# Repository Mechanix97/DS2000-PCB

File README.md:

<h1 align="center">DS2000 PCB</h1>

<p align="center">
  <b>Three keys for Discord: mute, deafen, disconnect.</b><br>
  RP2350A · Kailh Choc V1 · RGB inside the switch · USB-C (by JLC or by hand) or a soldered cable · the board <i>is</i> the top face
</p>

KiCad design for the DS2000, a three-key Discord control deck. Mute and deafen are lit from
underneath by an RGB LED; disconnect has none. The board is also the device's visible top face: the
RP2350A, the logos and the legends are meant to be seen. It sits in a 3D-printed tray
([DS2000-Enclosure](https://github.com/Mechanix97/DS2000-Enclosure)).

| | |
|---|---|
| MCU | Raspberry Pi RP2350A |
| Keys | 3× Kailh Choc V1 (low profile) in a row, 18 mm pitch, soldered, MBK-style caps. The footprint also takes 3-pin MX switches, for prototypes |
| LEDs | 2× SK6805-EC20 (2.0 × 2.0 × 0.65 mm, WS2812-compatible), on top inside the LED window of the mute and deafen switches |
| Connector | USB-C receptacle J1 on the bottom, fitted by JLC (*standard* variant) or by hand (*economic*). Or a USB cable soldered to J3's pads on the bottom. USB 2.0 full speed |
| Board | 4 layers, 1.6 mm, 72 × 46 mm, black mask, ENIG. Every part but J1 on top, RP2350A on show; underneath J1, J3's wire pads, the debug pads and the test pads |
| Tool | **KiCad 10** |

Design decisions, block descriptions, BOM and open items: [`docs/design-rev-a.md`](docs/design-rev-a.md).

## In its enclosure

The same frame-style tray works flat on the desk or on a separate 7° wedge, held by magnets. The
board screws into it through its four corner holes.

<table>
  <tr>
    <td width="50%"></td>
    <td width="50%">
      <br>
      
    </td>
  </tr>
  <tr>
    <td>Exploded: four M2 screws, the board, the tray and the 7° wedge</td>
    <td>Flat, with the USB-C leaving straight back; and on the wedge, from the side</td>
  </tr>
</table>

## The board

| Top face, without switches | Underneath |
|---|---|
|  |  |
| The visible face: RP2350A, logos and legends | J1's USB-C, J3's wire pads, debug pads (SWD, BOOT, RST) and test pads (renders from before the 2026-10-23 review) |

### Close up

| | |
|---|---|
|  |  |
| **RP2350A on show**, with the flash, the 12 MHz crystal and the core regulator around it | **Light inside the switch**: the SK6805-EC20 sits in the Choc's LED window (switch hidden here); its 100 nF hides under the keycap |
|  |  |
| **Underneath**: only the debug pads, so JLC assembles one side | **Low profile**: Choc V1 with flat caps, keycap tops ~8.7 mm above the board |

<details>
<summary>More views</summary>

| With switches and keycaps | From the back |
|---|---|
|  |  |

</details>

### Schematic

One sheet, one box per block: USB input (USB-C or soldered cable) and ESD, 3.3 V regulator, RP2350A supplies, QSPI flash, crystal
and SWD, keys, and the LED chain with its 5 V level shifter.

## Pinout

The pinout is defined by the firmware (`DS2000-Firmware/include/pins.h`). Change it there first.

| Function | GPIO |
|---|---|
| Mute key | GP0 |
| Deafen key | GP1 |
| Disconnect key | GP2 |
| LED data (WS2812-compatible chain, via 5 V level shifter) | GP5 |

## Checks

```sh
kicad-cli sch erc --severity-all DS2000.kicad_sch
kicad-cli sch export netlist --format kicadsexpr -o /tmp/ds2000.net DS2000.kicad_sch
```

CI (KiBot) runs ERC and DRC with schematic parity on every change and fails on any new error.

## Manufacturing

Every change also builds the files to order the board from JLCPCB, with assembly (artifact
`kibot-out` of the KiBot workflow):

- `JLCPCB/`: gerbers and drill (zipped), BOM with LCSC numbers, placement (CPL) with JLC's rotation fixes
- `step/`: the populated board as STEP, origin at its centre, for the [enclosure](https://github.com/Mechanix97/DS2000-Enclosure)

Board options, parts and what to check before ordering: [`docs/design-rev-a.md`](docs/design-rev-a.md#bill-of-materials).

## Related repositories

- [DS2000](https://github.com/Mechanix97/DS2000): desktop application
- [DS2000-Firmware](https://github.com/Mechanix97/DS2000-Firmware): firmware
- [DS2000-Enclosure](https://github.com/Mechanix97/DS2000-Enclosure): enclosure (Fusion 360)

## License

Copyright Mechardo Labs 2025-2026.

| What | License |
|---|---|
| The hardware design: schematic, board, footprints, symbols, 3D models, KiBot configs, docs | **CERN-OHL-S-2.0**, the strongly reciprocal CERN Open Hardware Licence v2, see [`LICENSE`](LICENSE) |
| The scripts in [`tools/`](tools) | AGPL-3.0, see [`tools/LICENSE`](tools/LICENSE) |
| The fonts in [`fonts/`](fonts) | SIL Open Font License 1.1, see the `OFL-*.txt` files there |

This source describes Open Hardware and is licensed under the CERN-OHL-S v2. You may redistribute
and modify this source and make products using it under the terms of the CERN-OHL-S v2
(https://ohwr.org/cern_ohl_s_v2.txt). This source is distributed WITHOUT ANY EXPRESS OR IMPLIED
WARRANTY, INCLUDING OF MERCHANTABILITY, SATISFACTORY QUALITY AND FITNESS FOR A PARTICULAR PURPOSE.
Please see the CERN-OHL-S v2 for applicable conditions.

Source location: https://github.com/Mechanix97/DS2000-PCB. As per CERN-OHL-S v2 section 4, should
you produce hardware based on this source, you must where practicable maintain the Source Location
visible on the external case of the product or in its documentation.

The hardware moved from AGPL-3.0 to CERN-OHL-S-2.0 in #16: the GPL family talks about source and
object code, which do not map cleanly onto schematics, gerbers and boards. The app and the firmware
stay AGPL-3.0.

The DS2000 name and the DS2000 and Mechardo Labs logos are not covered by these licenses: their use
is governed by the [trademark policy](TRADEMARKS.md). Forks are welcome under a name of their own.

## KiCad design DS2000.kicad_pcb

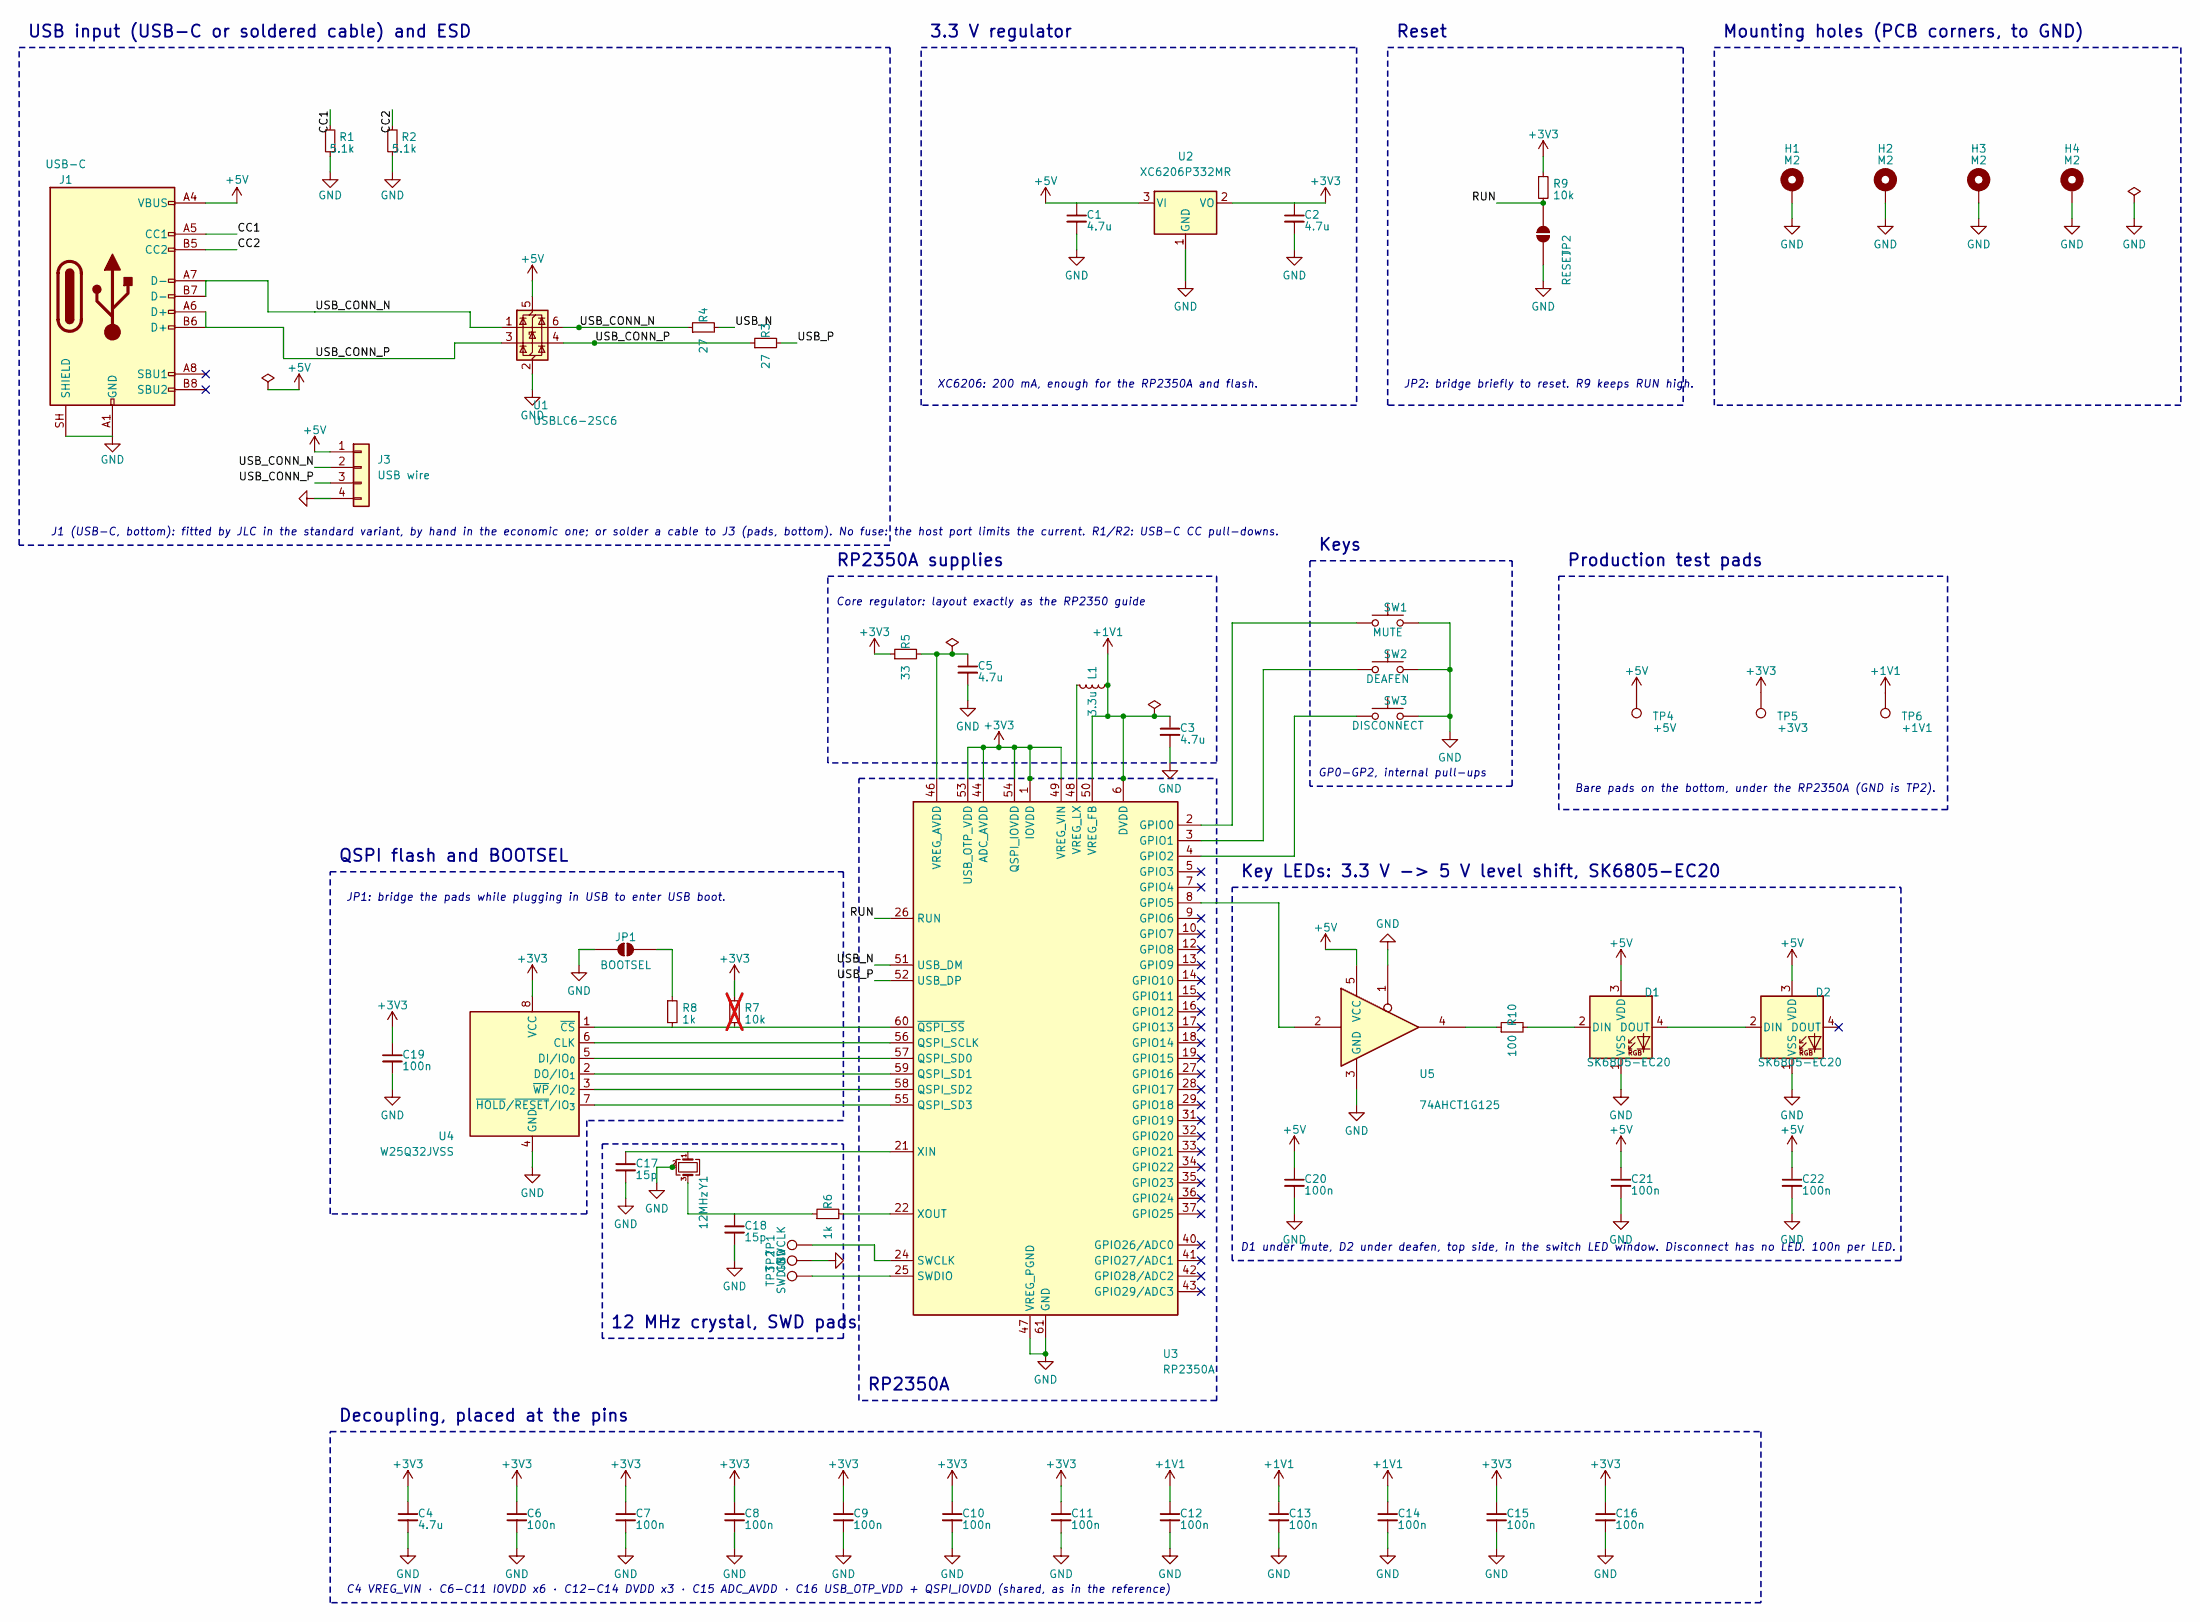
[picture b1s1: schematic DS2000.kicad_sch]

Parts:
C1, C2: 4.7u; C_0805_2012Metric; MPN CL21A475KAQNNNE; LCSC C1779
C3, C4: 4.7u; C_0402_1005Metric_Wide; MPN CL05A475MP5NRNC; LCSC C23733
C5: 4.7u; C_0402_1005Metric; MPN CL05A475MP5NRNC; LCSC C23733
C6, C7, C8, C9, C10, C11, C12, C13, C14, C15, C16, C19, C20, C21, C22: 100n; C_0402_1005Metric; MPN CL05B104KO5NNNC; LCSC C1525
C17, C18: 15p; C_0402_1005Metric; MPN 0402CG150J500NT; LCSC C1548
D1, D2: SK6805-EC20; LED_SK6805-EC20_2.0x2.0mm; MPN SK6805-EC20; LCSC C2890036
H1, H2, H3, H4: M2; MountingHole_2.2mm_M2_Pad_Via
J1: USB-C; USB_C_Receptacle_HRO_TYPE-C-31-M-12; MPN TYPE-C-31-M-12; LCSC C165948
J3: USB wire; WirePads_1x04_P2.54mm_SMD
JP1: BOOTSEL; SolderJumper-2_P1.3mm_Open_RoundedPad1.0x1.5mm
JP2: RESET; SolderJumper-2_P1.3mm_Open_RoundedPad1.0x1.5mm
L1: 3.3u; L_Abracon_AOTA-B201610S3R3-101-T; MPN AOTA-B201610S3R3-101-T; LCSC C42411119
R1, R2: 5.1k; R_0402_1005Metric; MPN 0402WGF5101TCE; LCSC C25905
R3, R4: 27; R_0402_1005Metric; MPN RC0402FR-0727RL; LCSC C138021
R5: 33; R_0402_1005Metric; MPN 0402WGF330JTCE; LCSC C25105
R6, R8: 1k; R_0402_1005Metric; MPN 0402WGF1001TCE; LCSC C11702
R7: 10k; R_0402_1005Metric; MPN 0402WGF1002TCE; LCSC C25744; not fitted
R9: 10k; R_0402_1005Metric; MPN 0402WGF1002TCE; LCSC C25744
R10: 100; R_0402_1005Metric; MPN 0402WGF1000TCE; LCSC C25076
SW1: MUTE; SW_Hybrid_Choc_V1_MX_1.00u
SW2: DEAFEN; SW_Hybrid_Choc_V1_MX_1.00u
SW3: DISCONNECT; SW_Hybrid_Choc_V1_MX_1.00u
TP1: SWCLK; TestPoint_Pad_D1.5mm
TP2: GND; TestPoint_Pad_D1.5mm
TP3: SWDIO; TestPoint_Pad_D1.5mm
TP4: +5V; TestPoint_Pad_D1.5mm
TP5: +3V3; TestPoint_Pad_D1.5mm
TP6: +1V1; TestPoint_Pad_D1.5mm
U1: USBLC6-2SC6; SOT-23-6; MPN USBLC6-2SC6; LCSC C2687116
U2: XC6206P332MR; SOT-23-3; MPN XC6206P332MR-G; LCSC C5446
U3: RP2350A; QFN-60-1EP_7x7mm_P0.4mm_EP3.4x3.4mm_ThermalVias_Drill0.3mm; MPN RP2350A; LCSC C42411118
U4: W25Q32JVSS; SOIC-8_5.3x5.3mm_P1.27mm; MPN W25Q32JVSSIQ; LCSC C179173
U5: 74AHCT1G125; SOT-353_SC-70-5; MPN SN74AHCT1G125DCKR; LCSC C350557
Y1: 12MHz; Crystal_SMD_3225-4Pin_3.2x2.5mm; MPN ABM8-272-T3; LCSC C20625731

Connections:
+1V1: C3.1, C12.1, C13.1, C14.1, L1.1, TP6.1, U3.6 (DVDD), U3.23 (DVDD), U3.39 (DVDD), U3.50 (VREG_FB)
+3V3: C2.1, C4.1, C6.1, C7.1, C8.1, C9.1, C10.1, C11.1, C15.1, C16.1, C19.1, R5.1, R7.1, R9.1, TP5.1, U2.2 (VO), U3.1 (IOVDD), U3.11 (IOVDD), U3.20 (IOVDD), U3.30 (IOVDD), U3.38 (IOVDD), U3.44 (ADC_AVDD), U3.45 (IOVDD), U3.49 (VREG_VIN), U3.53 (USB_OTP_VDD), U3.54 (QSPI_IOVDD), U4.8 (VCC)
+5V: C1.1, C20.1, C21.1, C22.1, D1.3 (VDD), D2.3 (VDD), J1.A4 (VBUS), J1.A9 (VBUS), J1.B4 (VBUS), J1.B9 (VBUS), J3.1, TP4.1, U1.5 (VBUS), U2.3 (VI), U5.5 (VCC)
/CC1: J1.A5 (CC1), R1.2
/CC2: J1.B5 (CC2), R2.2
/RUN: JP2.1 (A), R9.2, U3.26 (RUN)
/USB_CONN_N: J1.A7 (D-), J1.B7 (D-), J3.2, R4.1, U1.1 (I/O1), U1.6 (I/O1)
/USB_CONN_P: J1.A6 (D+), J1.B6 (D+), J3.3, R3.1, U1.3 (I/O2), U1.4 (I/O2)
/USB_N: R4.2, U3.51 (USB_DM)
/USB_P: R3.2, U3.52 (USB_DP)
GND: C1.2, C2.2, C3.2, C4.2, C5.2, C6.2, C7.2, C8.2, C9.2, C10.2, C11.2, C12.2, C13.2, C14.2, C15.2, C16.2, C17.2, C18.2, C19.2, C20.2, C21.2, C22.2, D1.1 (VSS), D2.1 (VSS), H1.1, H2.1, H3.1, H4.1, J1.A1 (GND), J1.A12 (GND), J1.B1 (GND), J1.B12 (GND), J1.SH (SHIELD), J3.4, JP1.1 (A), JP2.2 (B), R1.1, R2.1, SW1.2, SW2.2, SW3.2, TP2.1, U1.2 (GND), U2.1 (GND), U3.47 (VREG_PGND), U3.61 (GND), U4.4 (GND), U5.1, U5.3 (GND), Y1.2 (G), Y1.4 (G); also elsewhere on the board
unnamed: C18.1, R6.1, Y1.3
unnamed: D1.2 (DIN), R10.2
unnamed: D1.4 (DOUT), D2.2 (DIN)
unnamed: JP1.2 (B), R8.1
unnamed: R10.1, U5.4
unnamed: SW1.1, U3.2 (GPIO0)
unnamed: SW2.1, U3.3 (GPIO1)
unnamed: SW3.1, U3.4 (GPIO2)
unnamed: U3.8 (GPIO5), U5.2
unnamed: U3.56 (QSPI_SCLK), U4.6 (CLK)
unnamed: U3.57 (QSPI_SD0), U4.5 (DI/IO_{0})
unnamed: U3.59 (QSPI_SD1), U4.2 (DO/IO_{1})
unnamed: U3.58 (QSPI_SD2), U4.3 (~WP/IO_{2})
unnamed: U3.55 (QSPI_SD3), U4.7 (~HOLD/~RESET/IO_{3})
unnamed: TP1.1, U3.24 (SWCLK)
unnamed: TP3.1, U3.25 (SWDIO)
unnamed: C5.1, R5.2, U3.46 (VREG_AVDD)
unnamed: L1.2, U3.48 (VREG_LX)
unnamed: C17.1, U3.21 (XIN), Y1.1
unnamed: R6.2, U3.22 (XOUT)
unnamed: R7.2, R8.2, U3.60 (~QSPI_SS), U4.1 (~CS)

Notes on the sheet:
C4 VREG_VIN · C6-C11 IOVDD x6 · C12-C14 DVDD x3 · C15 ADC_AVDD · C16 USB_OTP_VDD + QSPI_IOVDD (shared, as in the reference)
3.3 V regulator
J1 (USB-C, bottom): fitted by JLC in the standard variant, by hand in the economic one; or solder a cable to J3 (pads, bottom). No fuse: the host port limits the current. R1/R2: USB-C CC pull-downs.
Keys
RP2350A
Reset
RP2350A supplies
D1 under mute, D2 under deafen, top side, in the switch LED window. Disconnect has no LED. 100n per LED.
12 MHz crystal, SWD pads
GP0-GP2, internal pull-ups
QSPI flash and BOOTSEL
Decoupling, placed at the pins
Core regulator: layout exactly as the RP2350 guide
Mounting holes (PCB corners, to GND)
JP1: bridge the pads while plugging in USB to enter USB boot.
JP2: bridge briefly to reset. R9 keeps RUN high.
Key LEDs: 3.3 V -> 5 V level shift, SK6805-EC20
XC6206: 200 mA, enough for the RP2350A and flash.
USB input (USB-C or soldered cable) and ESD
Production test pads
Bare pads on the bottom, under the RP2350A (GND is TP2).

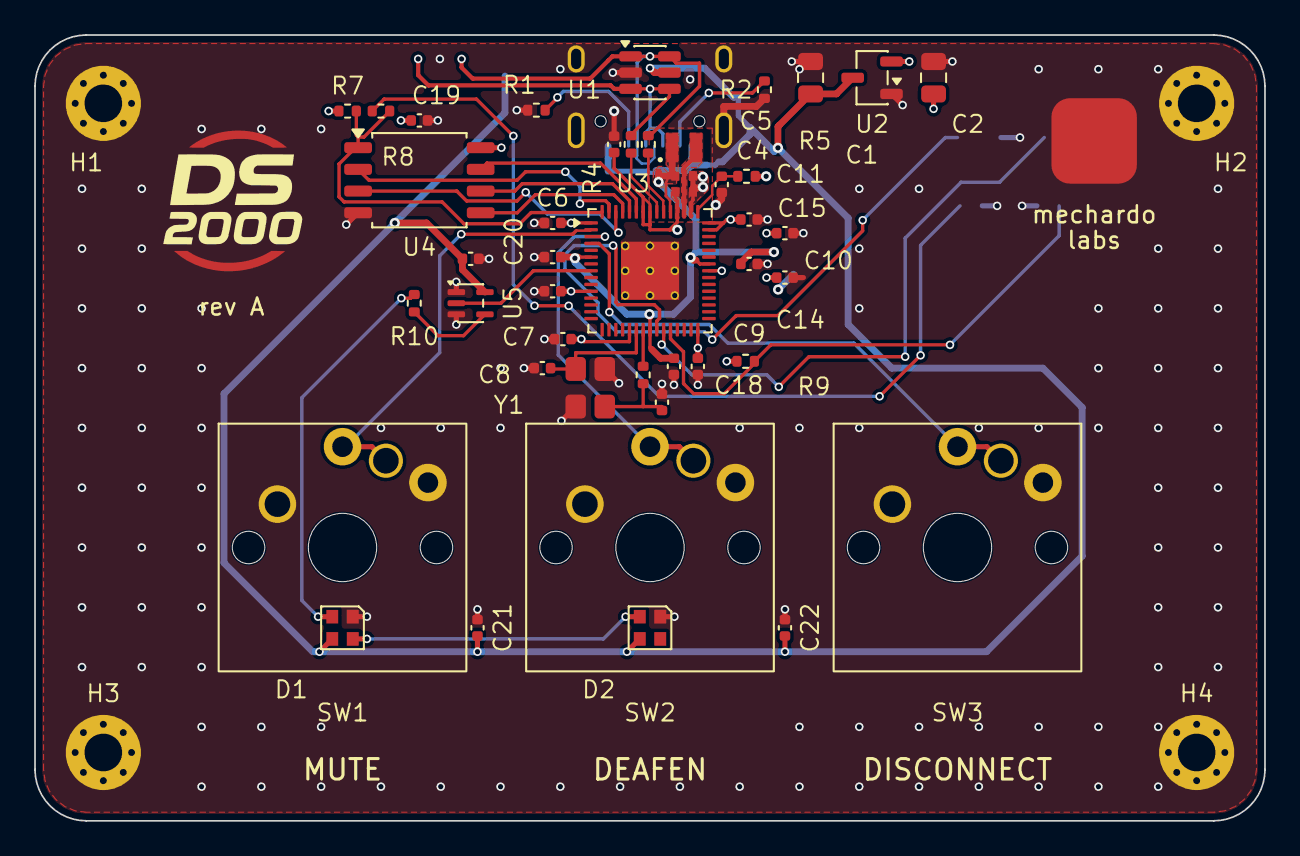
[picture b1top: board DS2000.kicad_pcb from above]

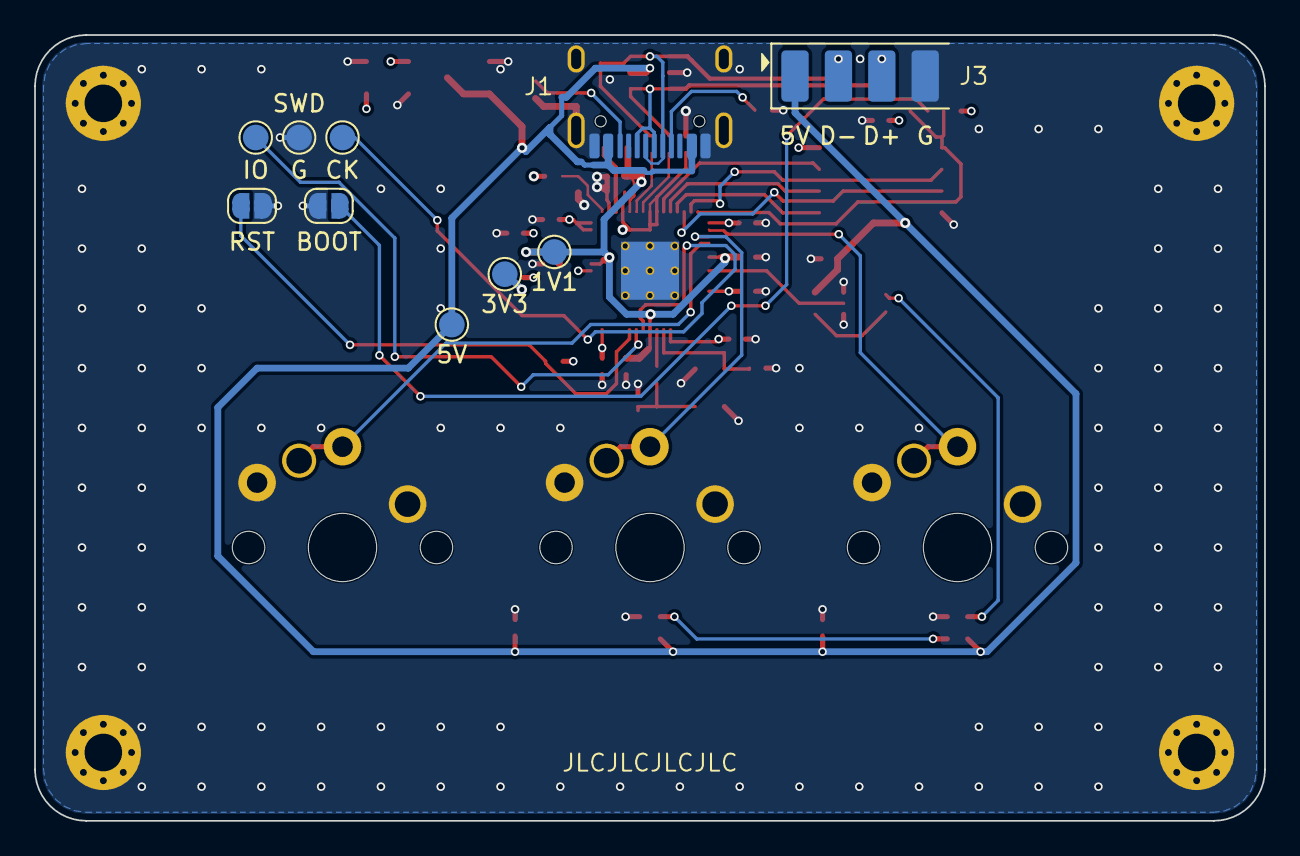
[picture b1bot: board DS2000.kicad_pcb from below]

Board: 4 copper layers, 72.0 x 46.0 mm, 60 parts (10 on the bottom side), 32 nets.

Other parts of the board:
LOGO1: Logo_Mechardo_5mm
LOGO2: Logo_DS2000_8.6mm

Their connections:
GND: LOGO1.1, LOGO2.1; also elsewhere on the board

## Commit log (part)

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2025-08-14 init
2025-08-14 init pcb
2025-08-14 more cahnges
2025-11-17 Create LICENSE
